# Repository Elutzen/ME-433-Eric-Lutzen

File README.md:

# ME-433-Eric-Lutzen
I don't know what to put here but github said I should put something.
Go Cats!

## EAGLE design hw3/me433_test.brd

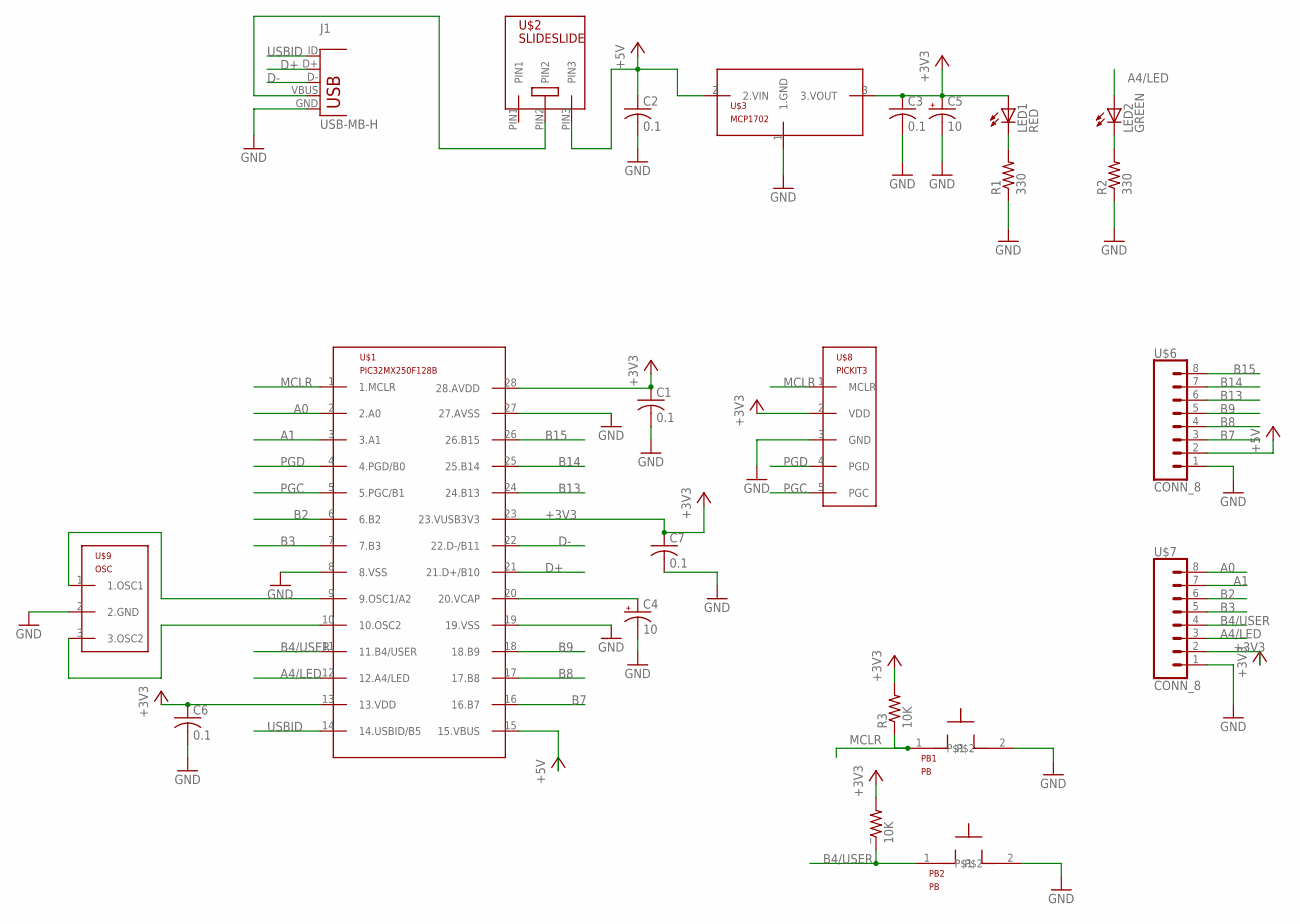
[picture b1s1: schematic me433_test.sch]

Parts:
C1, C2, C3, C6, C7: 0.1; C025-025X050
C4, C5: 10; B45181B
J1: USB-MB-H
LED1: RED; LED3MM
LED2: GREEN; LED3MM
PB1, PB2: PB
R1, R2: 330; 0207/10
R3: 10K; 0207/10
U$1: PIC32MX250F128B; DIL28-3
U$2: SLIDESLIDE; SLIDE
U$3: MCP1702; TO92
U$6, U$7: CONN_8; 1X08
U$8: PICKIT3; 1X05
U$9: OSC
_: 10K; 0207/10

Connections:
+3V3: C1.1, C3.1, C5.+, C6.1, C7.1, LED1.A, R3.2, U$1.13 (13.VDD), U$1.23 (23.VUSB3V3), U$1.28 (28.AVDD), U$3.3 (3.VOUT), U$7.2, U$8.2 (VDD), _.2
+5V: C2.1, U$1.15 (15.VBUS), U$2.PIN3, U$3.2 (2.VIN), U$6.2
A0: U$1.2 (2.A0), U$7.8
A1: U$1.3 (3.A1), U$7.7
A4/LED: LED2.A, U$1.12 (12.A4/LED), U$7.3
B2: U$1.6 (6.B2), U$7.6
B3: U$1.7 (7.B3), U$7.5
B4/USER: PB2.1, U$1.11 (11.B4/USER), U$7.4, _.1
B7: U$1.16 (16.B7), U$6.3
B8: U$1.17 (17.B8), U$6.4
B9: U$1.18 (18.B9), U$6.5
B13: U$1.24 (24.B13), U$6.6
B14: U$1.25 (25.B14), U$6.7
B15: U$1.26 (26.B15), U$6.8
D+: J1.D+, U$1.21 (21.D+/B10)
D-: J1.D-, U$1.22 (22.D-/B11)
GND: C1.2, C2.2, C3.2, C4.-, C5.-, C6.2, C7.2, J1.GND, PB1.2, PB2.2, R1.1, R2.1, U$1.8 (8.VSS), U$1.19 (19.VSS), U$1.27 (27.AVSS), U$3.1 (1.GND), U$6.1, U$7.1, U$8.3 (GND), U$9.2 (2.GND)
MCLR: PB1.1, R3.1, U$1.1 (1.MCLR), U$8.1 (MCLR)
unnamed: U$1.9 (9.OSC1/A2), U$9.1 (1.OSC1)
unnamed: U$1.10 (10.OSC2), U$9.3 (3.OSC2)
unnamed: J1.VBUS, U$2.PIN2
unnamed: C4.+, U$1.20 (20.VCAP)
unnamed: LED1.K (C), R1.2
unnamed: LED2.K (C), R2.2
PGC: U$1.5 (5.PGC/B1), U$8.5 (PGC)
PGD: U$1.4 (4.PGD/B0), U$8.4 (PGD)
USBID: J1.ID, U$1.14 (14.USBID/B5)

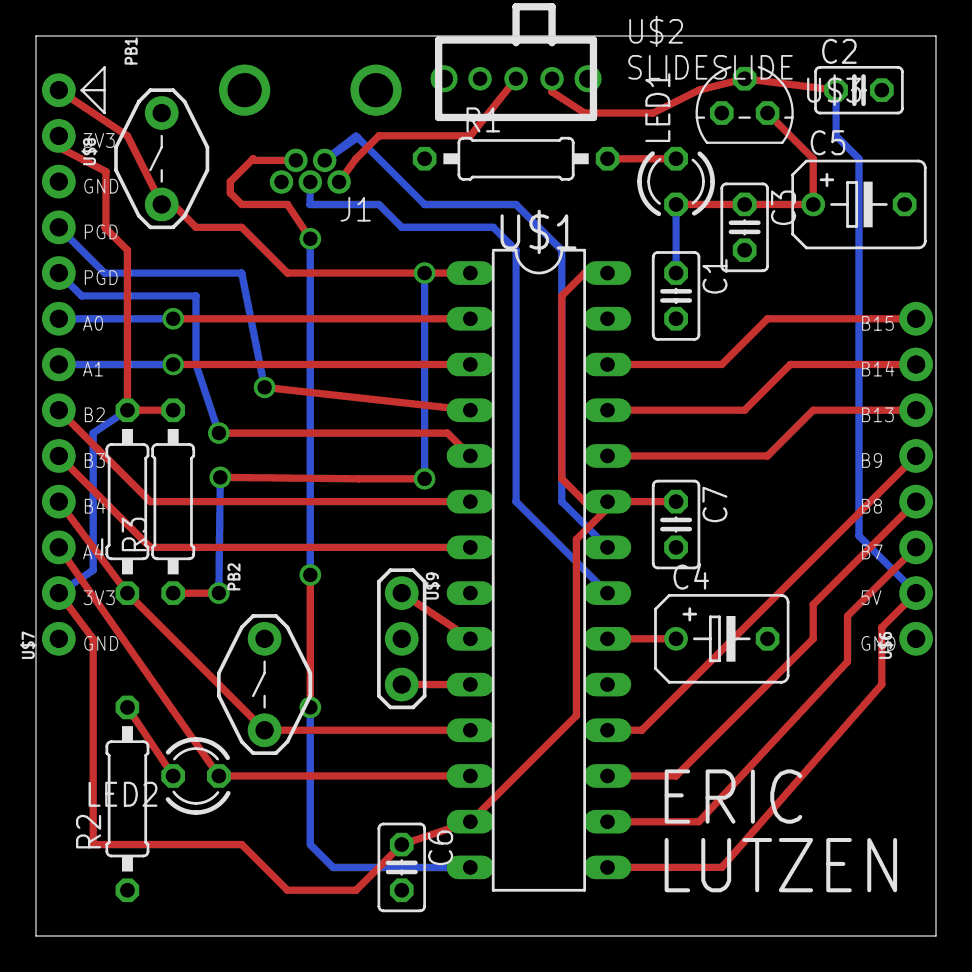
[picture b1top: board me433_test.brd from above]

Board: 2 copper layers, 50.0 x 50.0 mm, 23 parts (0 on the bottom side), 27 nets.

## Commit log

2017-03-29 :neckbeard: Added .gitattributes & .gitignore files
2017-03-29 Create HW1
2017-03-29 Revert ":neckbeard: Added .gitattributes & .gitignore files"
    This reverts commit 2a484cac1366eb2ec92b5b8cdba4a521fa5e0dce.
2017-03-30 Hello World Code
2017-03-30 adding pragmas to main.c
2017-03-30 updated pragma
2017-03-30 main function
    toggles LED at 1000 Hz unless button is pressed
2017-03-30 I forgot use use a microcontroller in MPLAB
2017-03-30 LED wasnt toggling at 1000 Hz forgot to reset counnter
2017-04-04 Merge remote-tracking branch 'origin/master'
    # Conflicts:
    # Hw1/HW1.X/main.c
2017-04-04 schematic
2017-04-05 toggle LED
2017-04-05 led still not toggling
2017-04-05 stuff
2017-04-06 board
2017-04-11 Start HW4
    made a pic_config header
2017-04-11 trying new things
    idk
2017-04-11 added hw4 to folder
    i should have done this sooner
2017-04-11 updating things
2017-04-11 wont build
2017-04-18 summary
2017-04-18 updating main file
2017-04-18 character writing function
2017-04-18 write strings
2017-04-18 troubleshooting
2017-04-20 changing sum stuff accel
2017-04-20 adding lcd stuff
2017-05-18 droid app 1
2017-05-28 done
2017-05-28 more stuff
2017-05-28 progress bar
2017-05-28 updated pic32.h
    updated
2017-05-28 asdf
    asdf
2017-05-28 accelerometer working
2017-05-28 working imu
2017-05-28 push it
2017-05-30 do it
